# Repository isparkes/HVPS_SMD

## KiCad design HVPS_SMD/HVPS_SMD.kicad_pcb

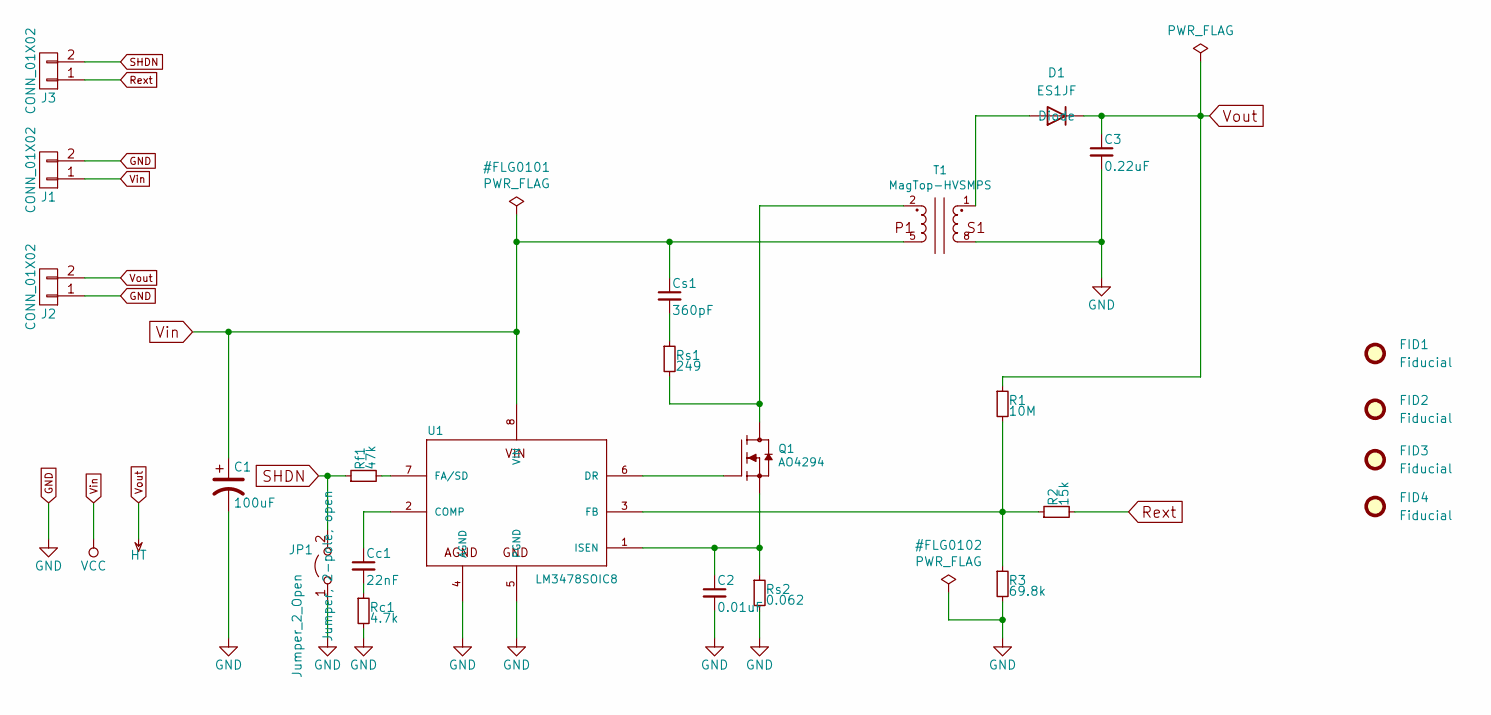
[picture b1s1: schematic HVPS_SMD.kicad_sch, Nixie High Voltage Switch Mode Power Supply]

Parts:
C1: 100uF; C_1210
C2: 0.01uF; C_0805_2012Metric
C3: 0.22uF; C_1210
Cc1: 22nF; C_0805_2012Metric
Cs1: 360pF; C_0805_2012Metric
D1: ES1JF; SMAF
FID1, FID2, FID3, FID4: Fiducial; Fiducial_0.75mm_Mask1.5mm
J1, J2, J3: CONN_01X02; Header_MA02-Edge-3.2
JP1: Jumper_2_Open; SolderJumper-2_P1.3mm_Open_Pad1.0x1.5mm_NoCtYd
Q1: AO4294
R1: 10M; R_0805
R2: 15k; R_0805
R3: 69.8k; R_0805
Rc1: 4.7k; R_0805
Rf1: 47k; R_0805
Rs1: 249; R_1206
Rs2: 0.062; R_1206_3216Metric
T1: MagTop-HVSMPS; WE-FLEX_ER11_5
U1: LM3478SOIC8; LM3478

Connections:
GND: C1.2, C2.2, C3.2, J1.2, J2.1, JP1.1 (A), R3.2, Rc1.2, Rs2.2, T1.8, U1.4 (AGND), U1.5 (PGND)
unnamed: Cc1.2, Rc1.1
unnamed: Cs1.2, Rs1.1
unnamed: D1.2 (A), T1.1
unnamed: Q1.5 (D), Q1.6 (D), Q1.7 (D), Q1.8 (D), Rs1.2, T1.2
unnamed: Q1.4 (G), U1.6 (DR)
unnamed: Cc1.1, U1.2 (COMP)
unnamed: Rf1.2, U1.7 (FA/SD)
unnamed: R1.2, R2.1, R3.1, U1.3 (FB)
unnamed: C2.1, Q1.1 (S), Q1.2 (S), Q1.3 (S), Rs2.1, U1.1 (ISEN)
Rext: J3.1, R2.2
SHDN: J3.2, JP1.2 (B), Rf1.1
Vin: C1.1, Cs1.1, J1.1, T1.5, U1.8 (VIN)
Vout: C3.1, D1.1 (K), J2.2, R1.1

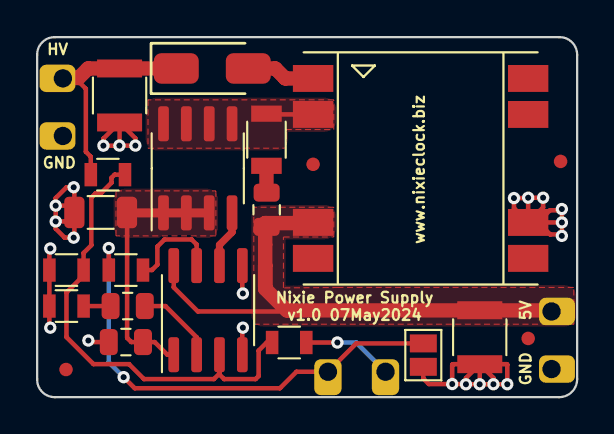
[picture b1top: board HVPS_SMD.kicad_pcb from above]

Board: 2 copper layers, 30.0 x 20.0 mm, 24 parts (0 on the bottom side), 14 nets.

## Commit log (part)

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2019-04-02 Clean up silk screen and DRC smells
2019-09-23 Change layer selection to add paste
2019-09-23 Remove old CAM files
2020-03-13 Changes to silk screen
2020-06-07 Prepare for Fab
2020-06-07 Custom footprint
2020-06-09 Add footprint for Vfix resistor R5
2020-06-12 More Fab
2020-06-12 Remove unwanted files
2020-06-12 Remove more unwanted files
2024-05-02 Update Kicad6
2024-05-02 Shrink
2024-05-02 More tidy up
2024-05-02 Add LCSC part numbers
2024-05-06 Chamfer corners
2024-05-07 Connectors for pin receptacles
2024-05-07 Minor SS
2024-05-09 Add fiducials and external control options
2024-05-10 Silk screen and QR Code
2024-05-17 Correct LCSC Part #
2024-05-28 Ignores
2024-05-29 Create hand assembly map
2024-05-31 Hand Assembly aid
2024-06-01 Hand Fabrication Map
2024-06-17 Improve efficiency
2024-09-24 Dimensions, fiducials
2024-09-24 Title blocks
2025-02-06 Documentation
2025-06-17 Update Kicad version
